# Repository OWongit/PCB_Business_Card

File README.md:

# NFC-Powered PCB Business Card

An interactive, battery-free printed circuit board that functions as a digital business card. 

This board utilizes Near Field Communication (NFC) to wirelessly transmit contact information, a portfolio link, or a vCard to any NFC-enabled smartphone. Additionally, the circuit harvests energy from the scanning device's RF field to illuminate LEDs, providing visual feedback when the card is being read.

## Features

* **Passive NFC Connectivity:** Uses an NTAG series IC to store NDEF formatted data (URLs, Text, Contact Info). No battery required.
* **Energy Harvesting:** On-board LEDs light up instantaneously when the card is brought within the RF field of a reader/phone.
* **Hybrid Design:**
    * **Front:** Clean aesthetic with LED indicators and antenna design.
    * **Back:** Silkscreen/Soldermask QR code for scanning.
* **Compact Form Factor:** Standard credit card dimensions (85.6mm x 54mm).

### Business Card Front

### Layout View

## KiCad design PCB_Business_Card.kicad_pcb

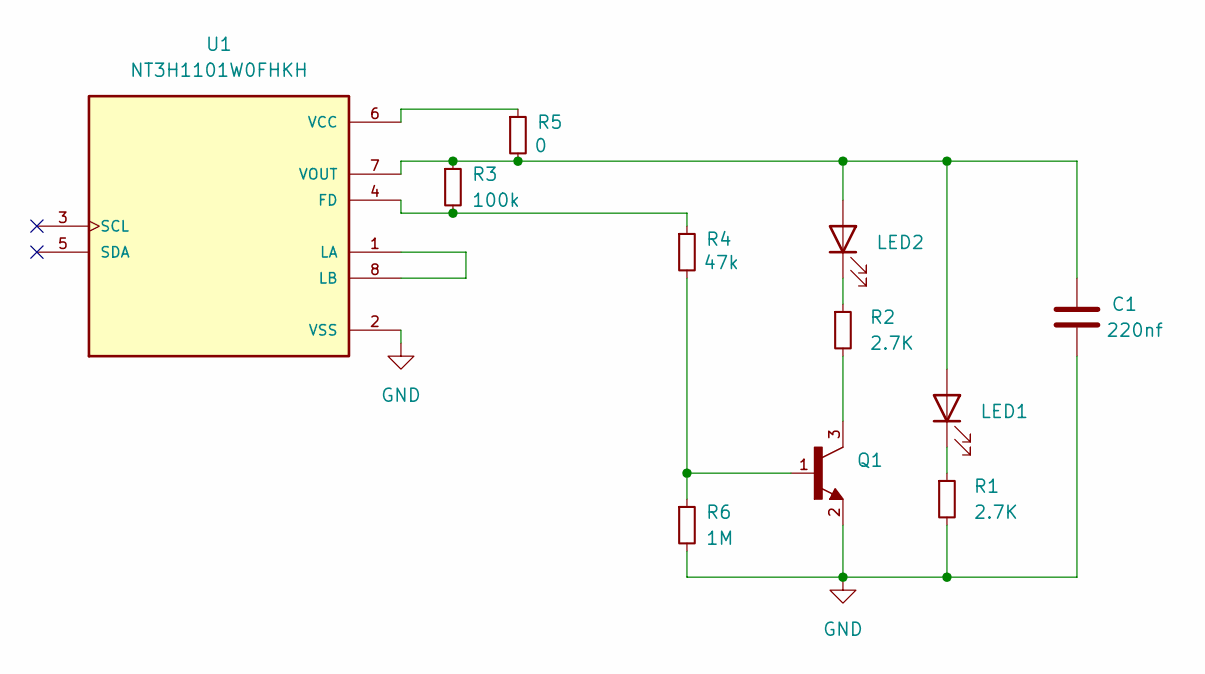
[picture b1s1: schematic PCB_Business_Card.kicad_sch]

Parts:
C1: 220nf; C_0402_1005Metric
LED1, LED2: LED; LED_0402_1005Metric
Q1: TRANS_PMBT3904_215
R1, R2: 2.7K; R_0402_1005Metric
R3: 100k; R_0402_1005Metric
R4: 47k; R_0402_1005Metric
R5: 0; R_0402_1005Metric
R6: 1M; R_0402_1005Metric
U1: NT3H1101W0FHKH; IC_NT3H1101W0FHKH; PARTREV 3.3

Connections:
GND: C1.2, Q1.2, R1.2, R6.2, U1.2 (VSS)
unnamed: C1.1, LED1.2 (A), LED2.2 (A), R3.1, R5.2, U1.7 (VOUT)
unnamed: LED1.1 (K), R1.1
unnamed: LED2.1 (K), R2.1
unnamed: Q1.1, R4.2, R6.1
unnamed: Q1.3, R2.2
unnamed: R3.2, R4.1, U1.4 (FD)
unnamed: U1.1 (LA), U1.8 (LB)
unnamed: R5.1, U1.6 (VCC)

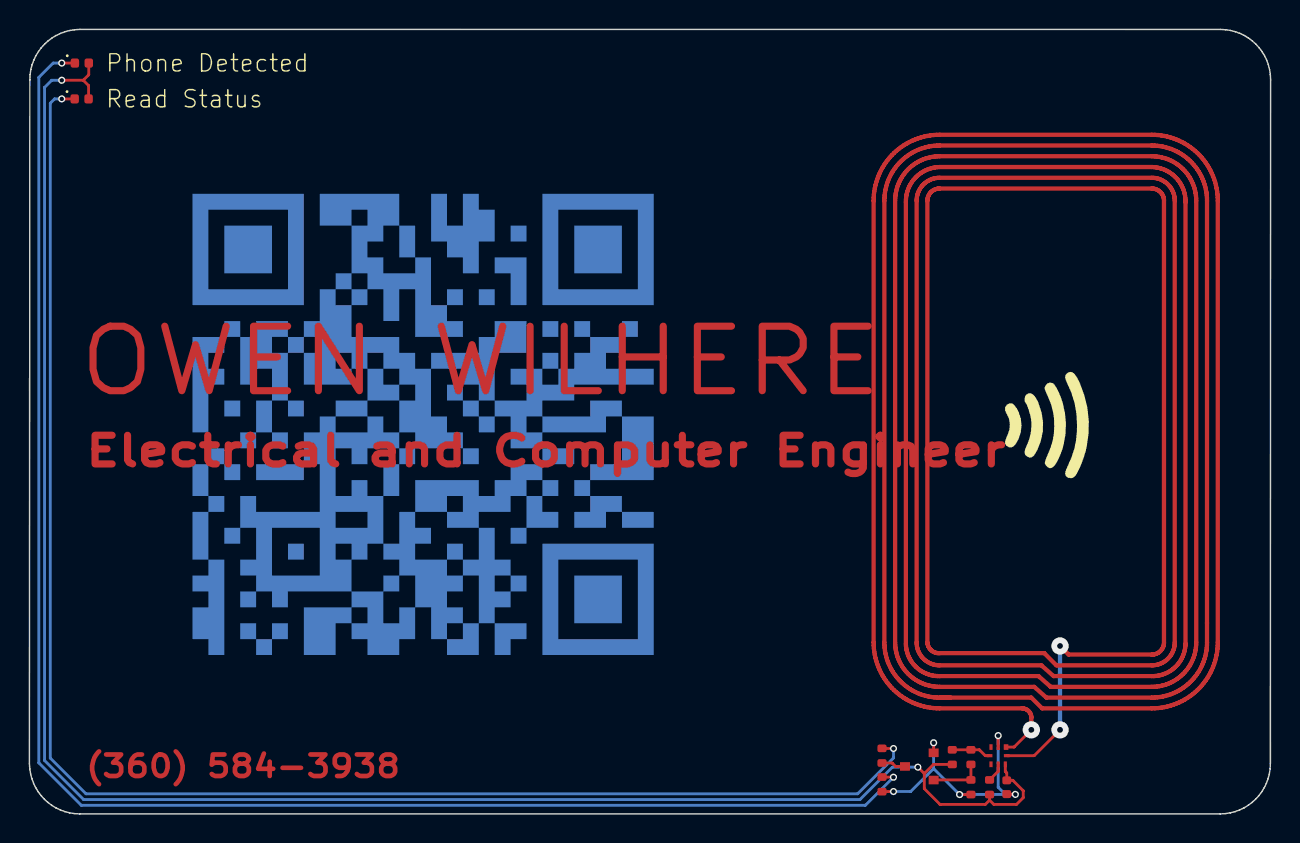
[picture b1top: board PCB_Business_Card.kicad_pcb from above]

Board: 2 copper layers, 86.6 x 54.7 mm, 11 parts (0 on the bottom side), 9 nets.

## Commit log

2026-01-15 Added Files
